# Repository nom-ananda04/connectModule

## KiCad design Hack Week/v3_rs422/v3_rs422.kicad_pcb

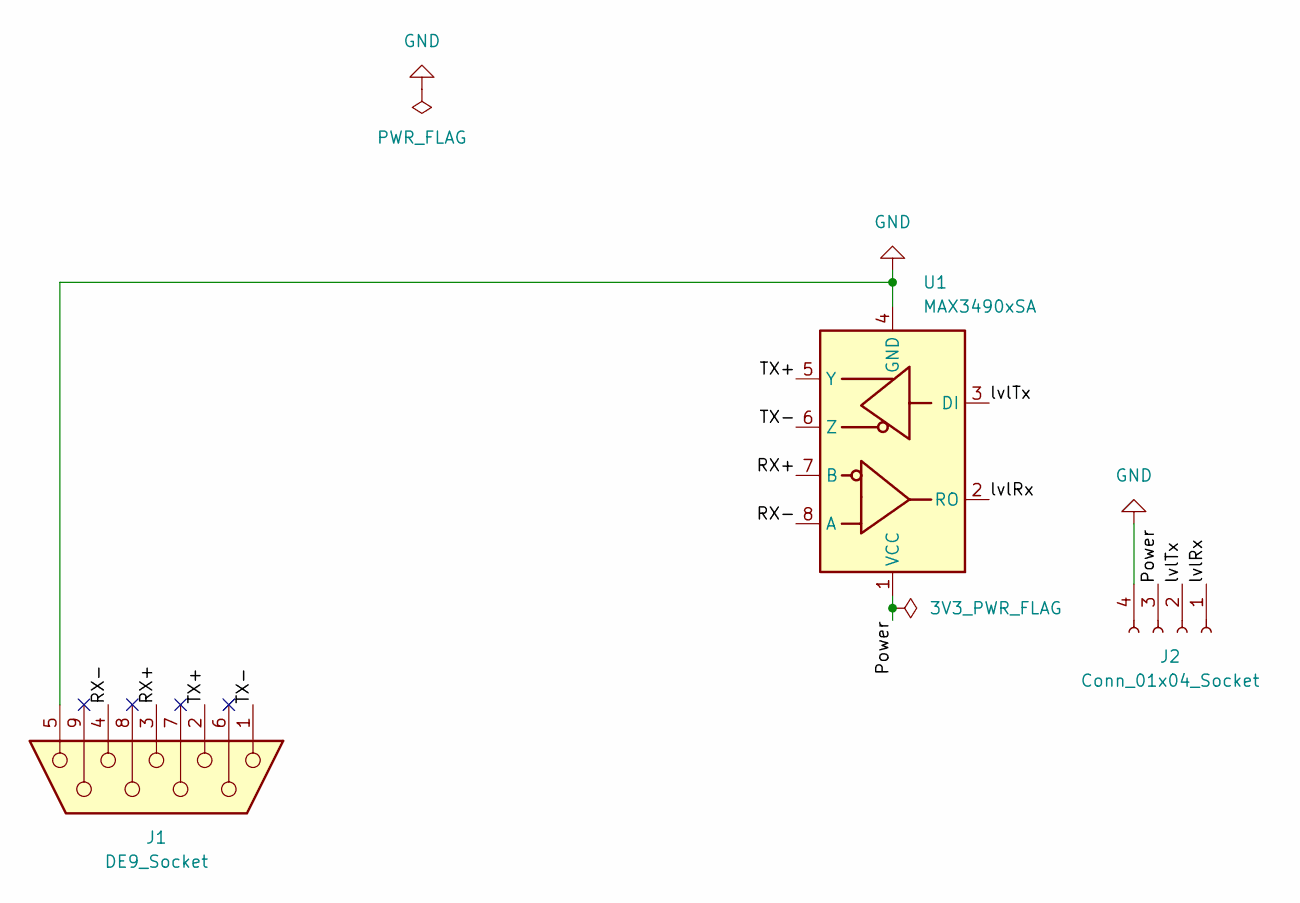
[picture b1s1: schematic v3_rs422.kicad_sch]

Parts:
J1: DE9_Socket; DSUB-9_Socket_EdgeMount_P2.77mm
J2: Conn_01x04_Socket; PinSocket_1x04_P2.54mm_Vertical
U1: MAX3490xSA; SOIC-8_3.9x4.9mm_P1.27mm

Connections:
/Power: J2.3, U1.1 (VCC)
/RX+: J1.3, U1.7 (B)
/RX-: J1.4, U1.8 (A)
/TX+: J1.2, U1.5 (Y)
/TX-: J1.1, U1.6 (Z)
/lvlRx: J2.1, U1.2 (RO)
/lvlTx: J2.2, U1.3 (DI)
GND: J1.5, J2.4, U1.4 (GND)

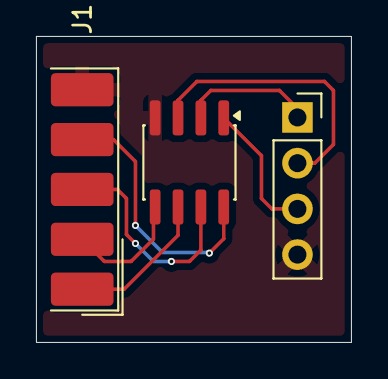
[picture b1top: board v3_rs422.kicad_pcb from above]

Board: 2 copper layers, 17.5 x 17.0 mm, 3 parts (0 on the bottom side), 8 nets.

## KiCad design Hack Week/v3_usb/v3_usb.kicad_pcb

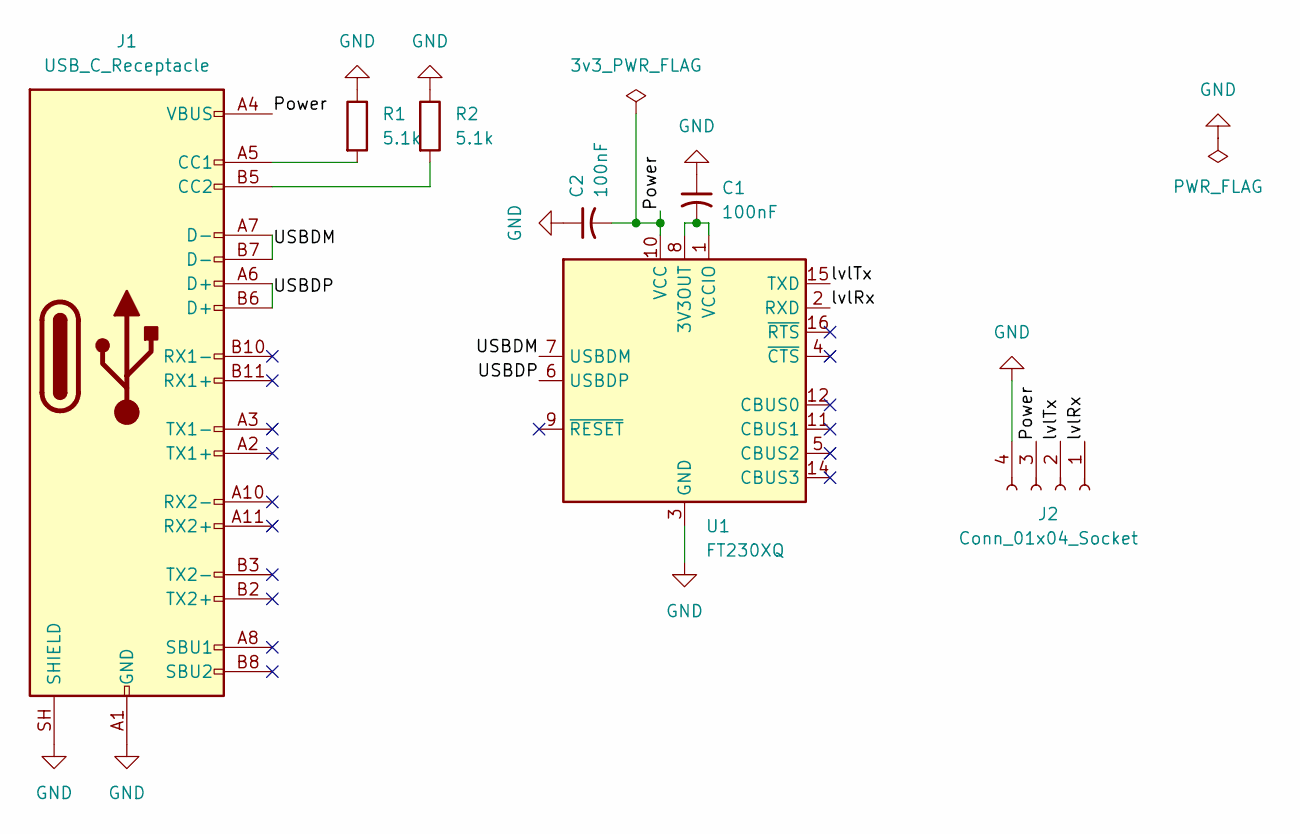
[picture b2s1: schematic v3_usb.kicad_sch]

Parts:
C1, C2: 100nF; C_0603_1608Metric
J1: USB_C_Receptacle; USB_C_Receptacle_Amphenol_12401948E412A
J2: Conn_01x04_Socket; PinSocket_1x04_P2.54mm_Vertical
R1, R2: 5.1k; R_0603_1608Metric
U1: FT230XQ; QFN-16-1EP_4x4mm_P0.65mm_EP2.1x2.1mm

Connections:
/Power: C2.2, J1.A4 (VBUS), J1.A9 (VBUS), J1.B4 (VBUS), J1.B9 (VBUS), J2.3, U1.10 (VCC)
/USBDM: J1.A7 (D-), J1.B7 (D-), U1.7 (USBDM)
/USBDP: J1.A6 (D+), J1.B6 (D+), U1.6 (USBDP)
/lvlRx: J2.1, U1.2 (RXD)
/lvlTx: J2.2, U1.15 (TXD)
GND: C1.1, C2.1, J1.A1 (GND), J1.A12 (GND), J1.B1 (GND), J1.B12 (GND), J1.SH (SHIELD), J2.4, R1.1, R2.1, U1.3 (GND), U1.13 (GND), U1.17 (GND)
unnamed: J1.A5 (CC1), R1.2
unnamed: J1.B5 (CC2), R2.2
unnamed: C1.2, U1.1 (VCCIO), U1.8 (3V3OUT)

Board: 2 copper layers, 7 parts (0 on the bottom side), 9 nets, no tracks yet.

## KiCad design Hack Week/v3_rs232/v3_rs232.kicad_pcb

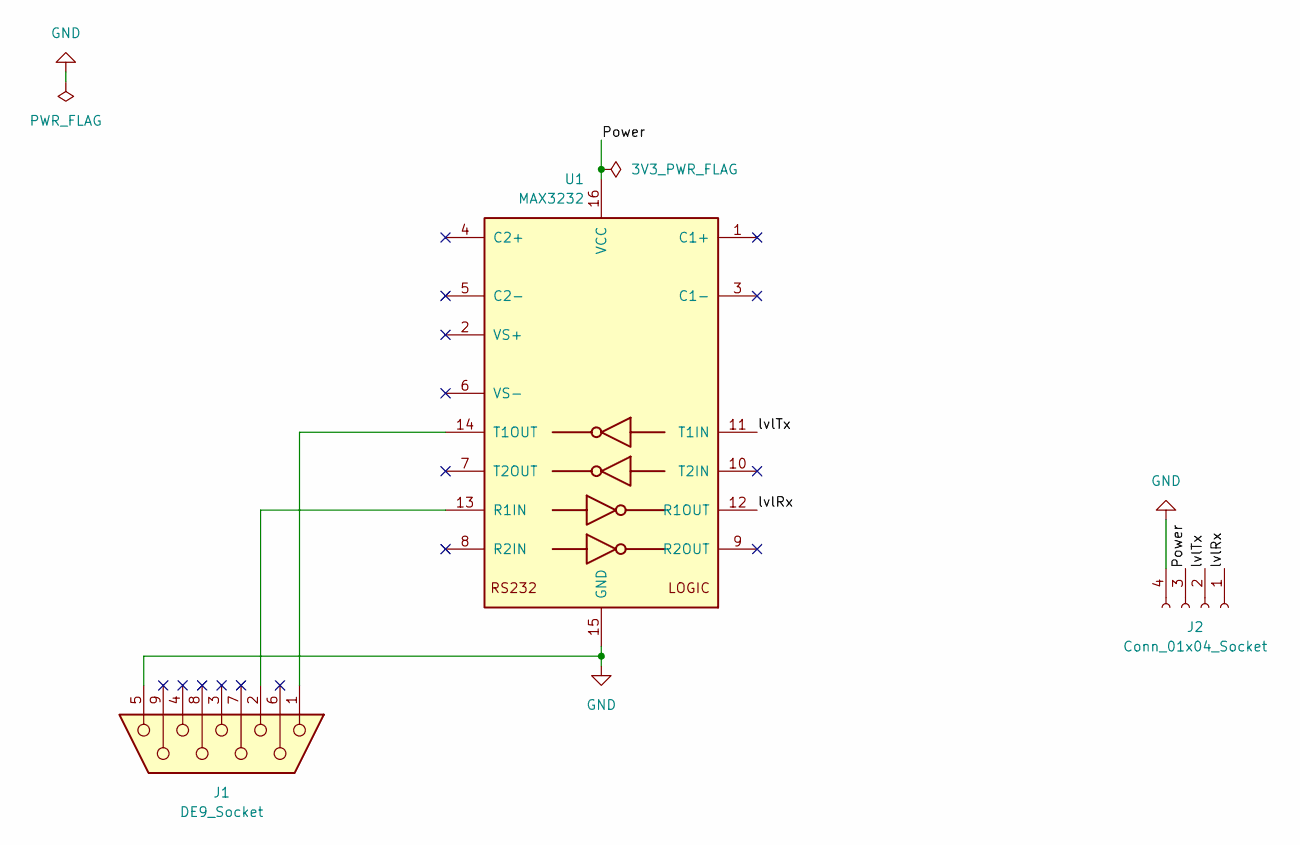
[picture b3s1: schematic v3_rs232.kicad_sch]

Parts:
J1: DE9_Socket; DSUB-9_Socket_EdgeMount_P2.77mm
J2: Conn_01x04_Socket; PinSocket_1x04_P2.54mm_Vertical
U1: MAX3232; TSSOP-16_4.4x5mm_P0.65mm

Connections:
/Power: J2.3, U1.16 (VCC)
/lvlRx: J2.1, U1.12 (R1OUT)
/lvlTx: J2.2, U1.11 (T1IN)
GND: J1.5, J2.4, U1.15 (GND)
unnamed: J1.2, U1.13 (R1IN)
unnamed: J1.1, U1.14 (T1OUT)

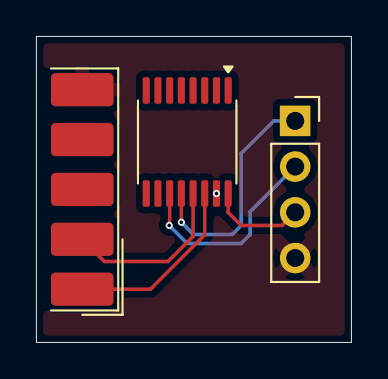
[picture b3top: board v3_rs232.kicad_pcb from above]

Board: 2 copper layers, 17.5 x 17.0 mm, 3 parts (0 on the bottom side), 6 nets.

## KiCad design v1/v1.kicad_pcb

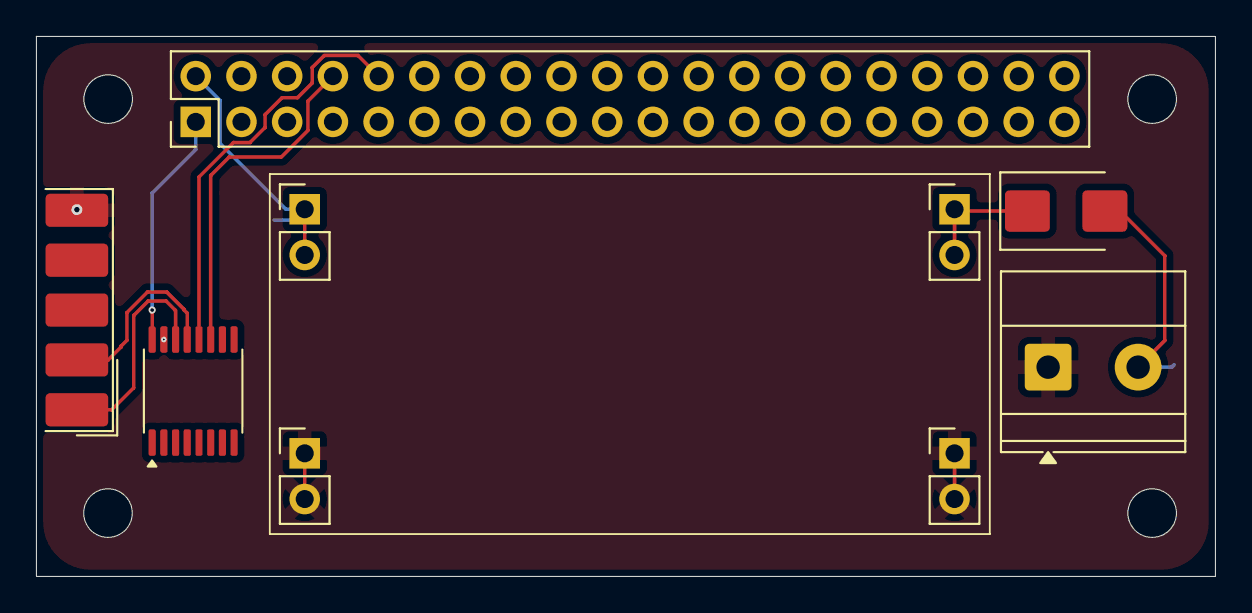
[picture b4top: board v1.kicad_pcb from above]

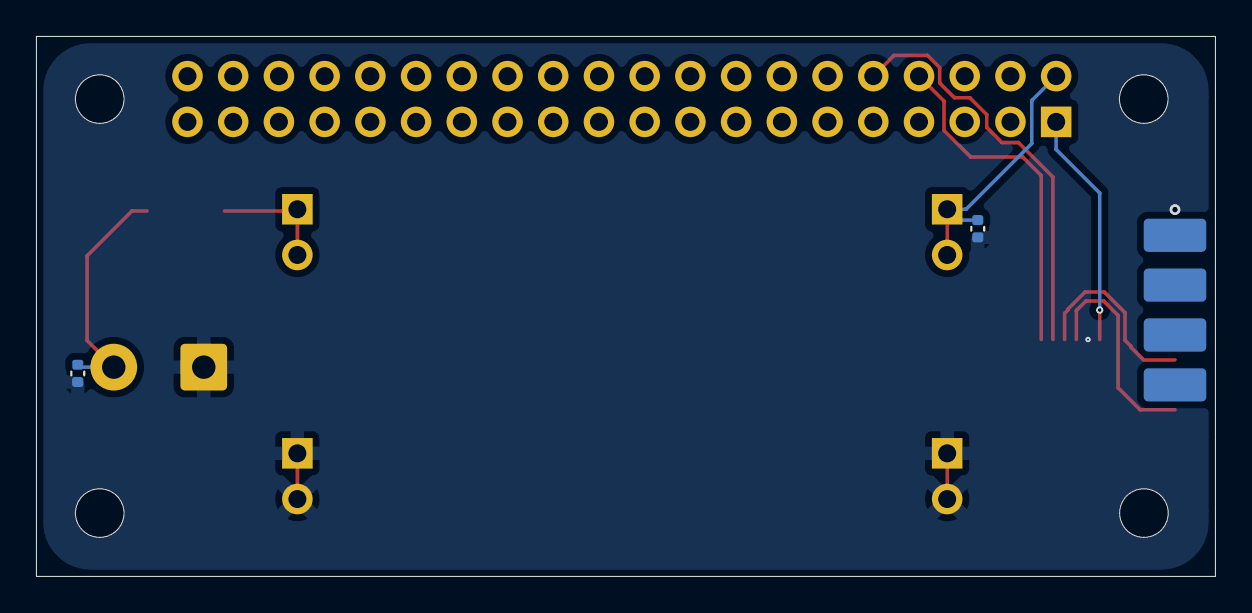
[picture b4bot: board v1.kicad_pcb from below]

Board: 2 copper layers, 65.5 x 30.0 mm, 15 parts (2 on the bottom side), 9 nets.

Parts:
C1, C2: C_Small; C_0402_1005Metric
D1: D_Schottky; D_SMB
H1, H2, H3, H4: MountingHole; MountingHole_2.7mm_M2.5
J1: DE9_Socket; DSUB-9_Socket_EdgeMount_P2.77mm
J2: Screw_Terminal_01x02; TerminalBlock_Phoenix_MKDS-1,5-2_1x02_P5.00mm_Horizontal
J3, J4, J5, J6: Conn_01x02_Pin; PinHeader_1x02_P2.54mm_Vertical
J7: Conn_02x20_Odd_Even; PinHeader_2x20_P2.54mm_Vertical
U1: MAX3232; TSSOP-16_4.4x5mm_P0.65mm

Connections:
/TPS54560/VIN: D1.1 (K), J4.1, J4.2
/TPS54560/VOUT: C2.1, J6.1, J6.2, J7.2
/lvlRx: J7.10, U1.12 (R1OUT)
/lvlTx: J7.8, U1.11 (T1IN)
GND: C1.2, C2.2, J1.5, J2.1, J3.1, J3.2, J5.1, J5.2, U1.15 (GND)
unnamed: C1.1, D1.2 (A), J2.2
unnamed: J7.1, U1.16 (VCC)
unnamed: J1.2, U1.13 (R1IN)
unnamed: J1.1, U1.14 (T1OUT)

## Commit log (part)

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2026-06-17 new boards pushing to git
2026-06-19 fixed footprints on v1
2026-06-22 adding more electrical isolation
2026-06-22 minor changes
